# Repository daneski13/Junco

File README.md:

<h1 align="center">Junco</h1>

Named after a small North American bird, Junco is a 60% Raspberry Pi Pico powered split keyboard boasting a 4x6 layout with an aggressive columnar stagger, 2-4 rotary encoders, and per-key RGB lighting.

Want to contribute? Check out [Contributing](./CONTRIBUTING.md).

Junco is inspired by the excellent [crkbd](https://github.com/foostan/crkbd), [Iris](https://keeb.io/collections/iris-split-ergonomic-keyboard/products/iris-keyboard-split-ergonomic-keyboard), [Kimiko](https://github.com/Keycapsss/Kimiko), [Sofle](https://github.com/josefadamcik/SofleKeyboard), and [Ferris](https://github.com/pierrechevalier83/ferris) keyboards. Massive thanks to [@JellyTitan](https://github.com/JellyTitan) for the wiring overhaul.

- [Design Philosophy and Quirks](#design-philosophy-and-quirks)
  - [Philosophy](#philosophy)
  - [Quirks](#quirks)
- [Build Guide / Assembly](#build-guide--assembly)
  - [Parts](#parts)
    - [Required](#required)
    - [Optional - RGB](#optional---rgb)
  - [Soldering](#soldering)
    - [Diodes](#diodes)
    - [RGB (Optional)](#rgb-optional)
    - [Pico](#pico)
    - [Hot-swap Sockets](#hot-swap-sockets)
    - [TRRS jack and Rotary Encoders](#trrs-jack-and-rotary-encoders)
  - [Case](#case)
  - [Flashing the firmware](#flashing-the-firmware)
- [Troubleshooting](#troubleshooting)
  - [No LEDs are working](#no-leds-are-working)
  - [Some LEDs are not working](#some-leds-are-not-working)
  - [An entire row or column of keys is not working](#an-entire-row-or-column-of-keys-is-not-working)
  - [Random key or keys not working](#random-key-or-keys-not-working)

## Design Philosophy and Quirks

### Philosophy

In my search for an ergonomic split keyboard, I came across several great keyboards, but I craved a combination of features and ideas from several with my own flavor. Iris' aesthetics, Kimiko's stagger and layout, elements of Ferris' philosophy.

I also wanted to use Raspberry Pi Picos for the controller as it has many advantages over the ProMicro that is normally used in custom keyboards. At the time, Pico powered keyboards were not yet really a thing and weren't yet supported by the main QMK branch. Thus, I created my own keyboard.

The Junco was designed around a set of goals, similar in vain to the Ferris.

**Goals:**

- Low-Cost
- Raspberry Pi Pico / RP2040
  - Superior flash storage and processing power compared to the common ATMega32 ProMicro
  - Faster than STM32 blackpill with more flash storage at the same cost or less
- Comfort
  - Aggressive Columnar Stagger
- Aesthetics
  - Almost all soldering done on the backside of PCB, optional RGB
- 60% layout
  - Near perfect blend of compactness and easy use without crazy combos or layer gymnastics
- Multiple rotary encoder support
- Hot-swap switches
- Plug and play either side of the split
  - Convenience and traveling
  - Flexible cable management
- Minimal different parts and easy to source
  - No need to buy a different types of LEDs or diodes. No reset switches, capacitors, resistors etc. required.

**Non-goals:**

- Reversible PCB
  - Can make assembly confusing and more error prone
- Multi-switch support
  - MX switches should use MX spacing, Choc switches should use Choc spacing.
- OLED Support
  - OLEDs are an added cost and somewhat comprise the aesthetics in my opinion. Don't find useful for a keyboard, more of a novelty.

### Quirks

Being my first venture into keyboard design... Junco unfortunately suffers from a few "quirks" at the moment that may or may not bother you:

- The case files currently provided in this repo assume PCB mounted switches and uses a 3mm switch plate that is flush with the PCB. This presents some problems that a more proper suspended switch plate would not have:
  - Mounting the Pico on the backside with headers causes a bit of the header to be exposed on the front side of the PCB, so the switch plate provided in this repo will not sit flush with the PCB.
  - The TRRS jack is also soldered on the backside, causing another uneven surface for the switch plate.
  - Thus, material must be removed from the back of the switch plate in the proper places for a flush fit.
    - Heat-gunning the switch plate in the proper area, lining it up with the PCB, and squishing provides a quick and *dirty* solution if done correctly.
  - **PRs are welcome to improve upon the case files or to create new cases as I am a 3D design novice.** A proper fix would be to have the PCB rest on the middle section's lip about 1.5mm below the switch plate. This would also allow plate mounted switches to properly latch onto the switch plate.

## Build Guide / Assembly

### Parts

#### Required

Where "56-58" is the count, 58 is needed with 2 rotary encoders. subtract from 58 every additional encoder (4 encoders 56, with 3 encoders 57).

| Name                                 | Count                   | Remarks                                                                                                                                                                                                                                                                                                                                                                                                                                                     | Potential Storefront                                                                                                                                                                                                                                   |
| ------------------------------------ | ----------------------- | ----------------------------------------------------------------------------------------------------------------------------------------------------------------------------------------------------------------------------------------------------------------------------------------------------------------------------------------------------------------------------------------------------------------------------------------------------------- | ------------------------------------------------------------------------------------------------------------------------------------------------------------------------------------------------------------------------------------------------------ |
| PCB                                  | 2 (1 left and 1 right)  | PCBs can be ordered from manufacturers such as JLCPCB and LCSC                                                                                                                                                                                                                                                                                                                                                                                              |                                                                                                                                                                                                                                                        |
| MX Hot-swap Sockets                  | 56-58                   |                                                                                                                                                                                                                                                                                                                                                                                                                                                             |                                                                                                                                                                                                                                                        |
| Diodes                               | 62                      | Surface mount SOD-123 1N4148, _or_ through-hole 1N4148 diode. These are both common and inexpensive, any one should do. Through hole is usually easier to solder.                                                                                                                                                                                                                                                                                           | SMD: [AliExpress](https://www.aliexpress.us/item/2251832663565152.html) <br>[JLCPCB Part#: C2972760](https://jlcpcb.com/partdetail/3368026-1N4148SOD123/C2972760)<br> Through-hole: [AliExpress](https://www.aliexpress.us/item/2251832473773777.html) |
| Raspberry Pi Picos                   | 2                       | PCB is specifically designed with the official Pico and YD-2040 type clone in mind, however several [other clone types](https://docs.google.com/spreadsheets/d/1LPjy6F5lHfUkmsrM5zlZmc5auYy5YBakW8Awe6hYFWo) should be compatible (Waveshare, WeAct, EstarDyn, Tenstar). Also, the case is currently designed assuming the Pico is soldered with [headers](https://www.sparkfun.com/products/17907), but surface mounting the Pico is supported on the PCB. | [AliExpress, YD-2040](https://www.aliexpress.us/item/3256803909832318.html)                                                                                                                                                                            |
| TRRS Jacks                           | 2                       | PJ-320A                                                                                                                                                                                                                                                                                                                                                                                                                                                     | [AliExpress](https://www.aliexpress.us/item/2255800474897706.html)                                                                                                                                                                                     |
| TRRS Cable (3.5mm "Headphone" Cable) | 1                       | TRRS (4 pole) is currently required, not TRS (3 pole)                                                                                                                                                                                                                                                                                                                                                                                                       |                                                                                                                                                                                                                                                        |
| MX Style Switches                    | 56-58                   |                                                                                                                                                                                                                                                                                                                                                                                                                                                             |                                                                                                                                                                                                                                                        |
| Key Caps                             | 56-58                   |                                                                                                                                                                                                                                                                                                                                                                                                                                                             |                                                                                                                                                                                                                                                        |
| Rotary Encoders and Caps             | 2-4                     | EC-11 Rotary Encoder                                                                                                                                                                                                                                                                                                                                                                                                                                        | [AliExpress](https://www.aliexpress.us/item/2261799870168498.html)                                                                                                                                                                                     |
| M3 6mm or 6mm+ Screws and Nuts       | 8                       |                                                                                                                                                                                                                                                                                                                                                                                                                                                             |                                                                                                                                                                                                                                                        |
| Case                                 | 1 Left Set, 1 Right Set | Case files are located in the [case folder](./Case).                                                                                                                                                                                                                                                                                                                                                                                                        |                                                                                                                                                                                                                                                        |
| Micro USB Cable or USB-C Cable       | 1                       | USB cable for connecting the keyboard to your computer, dependent on what the Pico you chose uses.                                                                                                                                                                                                                                                                                                                                                          |                                                                                                                                                                                                                                                        |

#### Optional - RGB

These parts are necessary for the RGB lighting.

| Name                                          | Count | Remarks                                                                                                                                                                            | Potential Storefront                                                                                                                                                 |
| --------------------------------------------- | ----- | ---------------------------------------------------------------------------------------------------------------------------------------------------------------------------------- | -------------------------------------------------------------------------------------------------------------------------------------------------------------------- |
| 74AHCT1G125 Voltage Level Shifter/ Bus Buffer | 2     | SOT23-5 Footprint <br/> <br/> Required for LEDs to work properly, Pico runs at 3.3V while the LEDs will require 5V                                                                 | [AliExpress](https://www.aliexpress.us/item/3256803831434811.html) <br> [JLCPCB Part# C7484](https://jlcpcb.com/partdetail/TexasInstruments-SN74AHCT1G125DBVR/C7484) |
| RGB SMD LEDs (Prefer SK6803MINI-E)            | 74    | The 3MA SK6803MINI-E is highly recommended over the more traditional 12MA SK6812MINI-E due to its smaller current draw, allowing the LEDs to be very bright at manageable wattage. | [AliExpress](https://www.aliexpress.us/item/3256803450292556.html) <br> [JLCPCB Part# C5184589](https://jlcpcb.com/partdetail/Normand-SK6803MINIE/C5184589)          |

### Soldering

The PCB is not reversible, there is a dedicated right and left half in the KiCad PCB files. Almost all of the soldering will occur on the backside of the PCB. 

#### Diodes

Solder the diodes as you see in the photo.
SMD diodes are soldered on the back of the board. 
Through-hole diodes are inserted on the back of the board, and soldered on the front.

> [!WARNING]
> **Note** that the diodes have polarity, ensure the line on the diode matches the silkscreen.

#### RGB (Optional)

All LEDs must be soldered to the PCB for RGB to work properly, even if you will not be using backlight or will be using an encoder that covers an LED. (They are wired in serial).

First solder the level shifter. It's tiny & squirrley - [drag soldering](https://www.youtube.com/watch?v=wUyetZ5RtPs)" is a good method. See photo:

All LEDs will be soldered facing _down into the board_. The LEDS for per-key RGB will be soldered on the back of the board, while the LED's for the underglow will be soldered on the front of the board.

> [!WARNING]
> **Note** the LED orientation is very important. One of the pads on each LED (the ground pin) will be misshapen relative to the others, this pad should connect to the PCB pad that is marked by the L shape on the silkscreen. For a sanity check, a corner of the LED's front-side will also be "cut", this corner must also line up with the L shape on the silkscreen.

 Blue is LEDs that will be installed on the underside of the board, facing the front-side of the PCB for the per-key lighting. Red will be installed on the front of the board for the underglow:

Per Key leds soldered on the backside, while underglow LEDs ssoldered on the opposite side:

Ground pin orientation:

After you finish the next step of soldering the Pico to the PCB, recommend plugging the keyboard in and flashing QMK to ensure the LEDs are lighting up. If there are any issues, check the troubleshooting section.

#### Pico

If you are soldering the Pico surface mount style, go ahead with soldering it to the backside of the PCB and you can skip to the next section.

If you are soldering the Pico using headers, first solder the Pico to the headers and then the header/Pico to the PCB. 

**Ensure that you are soldering the Pico/Header onto the backside of the PCB.**

The best way to go about this method is to rest the shorter end of the headers in the through-holes of the PCB on a flat surface and place the Pico on top, through the longer end of the header. This will stabilize the headers somewhat and ensure proper spacing. Solder the Pico to the 2 header pins on the both the "top" and "bottom" of the Pico to hold it in place. Proceed to solder the Pico to the rest of the header's pins.

After the Pico is soldered to the header, flip the PCB over and solder the sticking-out header pins to the PCB. Start with the 2 "top" and 2 "bottom" header pins to hold it in place, being sure to minimize the space between the header's plastic and the PCB. Proceed to solder the PCB to the rest of the header's pins.

The end result will look like this:

Backside of PCB:

Front-side of PCB:

#### Hot-swap Sockets

Place hot-swap sockets on the backside of the PCB and solder. See photo:

#### TRRS jack and Rotary Encoders

The process for soldering the TRRS jack and the process for the rotary encoders are very similar.

On the **backside** of the PCB, place the TRRS jack. On the front-side of the PCB, bend the pins of the TRRS jack to "latch" onto the PCB and solder.

Backside PCB:

Front-side PCB:

On the **front-side** of the PCB, place the rotary encoder(s). On the backside of the PCB, bend the pins of the encoder to "latch" onto the PCB and solder.

Front-side PCB:

Backside PCB:

### Case

At the moment, the case files included in the [case directory](./Case) support 3D printing of a case assuming PCB mounted switches (since the 3mm switch plate is resting on the PCB). Since I do not own or have easy access to a 3D printer, the case was designed to be easy to print with 3rd party printing services in-mind such as Treatstock.

Raw files are provided for designing your own case if you see fit. Further work on the case may occur in the future to properly suspend the switch plate. PRs are welcome.

The case is comprised of 4 parts, 8 M3 screws, and 8 M3 nuts.

To have a functional case you need the Bottom Left and Bottom Right along with a Left Switch Plate and a Right Switch Plate. 4 M3 screws and their nuts will hold the switch plate and bottom together for each side of the split. Recommend printing the bottom in white at 40% infill so the underglow LEDs can bleed through.

The naming schemes "- 2 Rotary" and "- 4 Rotary" are products of the raw files used to model the case.

The switch plates named "- 2 Rotary" assume 1 rotary encoder will be used on that side of the split. One by they thumb keys.

The switch plates named "- 4 Rotary" assume 2 rotary encoders will be used on that side of the split. One by the thumb keys and one in the far bottom corner

If you would like to have 3 rotary encoders rather than 2 total or 4 total you would use both variants. The side that will have 2 rotary encoders will use the "- 4 Rotary", while the other side with 1 rotary encoder will use the "- 2 Rotary".

As mentioned in [design quirks](#quirks), there are some problems with making the switch plate flush with the PCB. After you get it flush, you can completely assemble your keyboard! Assembly goes in the reverse of the following:

-- Keycaps --

-- Switches --

-- Case Switch Plate -- (screw + nut connect the plate with the bottom)

-- PCB --

-- Case Bottom --

### Flashing the firmware

Junco is powered by the QMK firmware, see the [build environment setup](https://docs.qmk.fm/#/getting_started_build_tools). Brand new to QMK? Start with the [Complete Newbs Guide](https://docs.qmk.fm/#/newbs).

For users wanting something a little more fun, check out my keymap folder [here](./qmk) and my keymap [here](./qmk/keymaps/deluxe).

Flashing instructions can be found [here](https://github.com/qmk/qmk_firmware/tree/master/keyboards/junco).

Congratulations and enjoy your split keyboard!

## Troubleshooting

### No LEDs are working

Try the following until problem solved:

1. Ensure the level shifter is properly soldered onto the PCB, re-solder as needed.
2. There is a diode without a corresponding switch located to the top right of the Pico on both sides of the split, check and re-solder that diode as needed.
    1. Short the pads on either side of the diode on both halves.
       1. If some the LEDs turn on, re-solder the diodes. Replace it if problem persists.
       2. If no LEDs turn on after shorting the diode's pads, there is likely a problem with the first LED, move to the next section for the first LED in the electrical order. If that still doesn't work, the level shifter is likely damaged and needs to be replaced.

### Some LEDs are not working

Go through the LED electrical order (pictured below) until you reach the problem LED. That LED **or** the one previous to it has a problem.

LED Electrical Order (1-8 are underglow):

Right side is identical but mirrored.

Try the following until problem solved:

1. Check that the pads of LED not turning on and its previous are soldered correctly, re-solder for a better connection as needed.
2. Double check that the LED not turning on is in the correct orientation.
3. If the soldering looks good and the orientation is correct, try re-soldering all the pads any way for good measure.
4. If re-soldering didn't work than the LED is likely dead or damaged in which case replace it.

### An entire row or column of keys is not working

In this case, there is most likely a problem with the PCB's connection to the Pico. Note that the bottom row of keys is staggered by 2, so the the corresponding matrix column is shifted.

Rows:

Cols:

The right side is identical but mirrored.

Try the following until problem solved:

1. Double check that you have soldered the Pico into the correct holes.
2. Ensure the soldering connections of the Pico to the PCB is good (if you used a header to solder the Pico onto the PCB one of the connections to the through-hole is likely bad). Re-solder as needed.
3. If none of the connections are obviously bad, use the image above to see what row/column corresponds to what connection (GP numbering on back of PCB). Re-solder that specific connection for good measure and test.
4. If re-soldering the connection didn't work, your Pico or PCB is likely damaged. Rule out the Pico by directly shorting the that row or column's corresponding pad on the Pico with another column/row pad (connecting one row and one column). If a key press is registered, there is a problem with your PCB, see the bottom of the next section about potentially fixing paths on the PCB. If no keypress is registered, the Pico is damaged and have fun de-soldering your Pico (hot-air station or careful work with a heat gun is the best way).

### Random key or keys not working

Note that the bottom row of keys is staggered by 2, so the the corresponding matrix column is shifted. See the photo in the above section.

If it's not a row or column of keys, than there is a bad connection between your switch and PCB.

Try the following until problem solved:

1. Re-seat the switch in the hot-swap socket.
2. Try a different switch.
3. Check the soldering of the hot-swap socket to the PCB, re-solder as needed
4. Short the PCB pads on either side of the hot-swap socket, if that registers a keypress, the hot-swap socket is bad and needs to replaced.
5. Check the diode.
   1. Check the soldering of the diode to the PCB and re-solder as needed.
   2. Double check that the diode is oriented correctly.
   3. Make sure diode actually works and has a good connection.
      1. Read the diode with a multimeter, typically reads a little more than 0.6. Higher numbers usually means the solder connection is bad, de-solder and re-solder the diode. If not reading, diode is bad and needs to be replaced.
      2. No multimeter? Short either side of the diode and press the key. If that works either the diode's connection is bad and re-solder, or the diode is dead and needs to be replaced.
6. If none of the above worked, the problem is most likely with the paths inside the PCB.
   1. You can try the following: (credit to [crkbd](https://github.com/foostan/crkbd) guide)
      1. "Visually inspect the PCB. If it looks scratched or damaged anywhere along the path from ProMicro to diode to keyswitch, the path might be interrupted. If you find a spot that looks damaged, you can use some wire to bypass the section that is damaged (e.g. connecting the ProMicro directly to the first pad of the diode). If this fixes the key, then you can either opt to keep the wire permanently, or you can try to repair the path. The path can be repaired by carefully scraping off the paint from a section of the path that is okay on either side of the damaged part (use a small flat head screwdriver intended for electronics). Then clean carefully with alcohol and solder a new connection. Youtube might have some guides on how to do this."

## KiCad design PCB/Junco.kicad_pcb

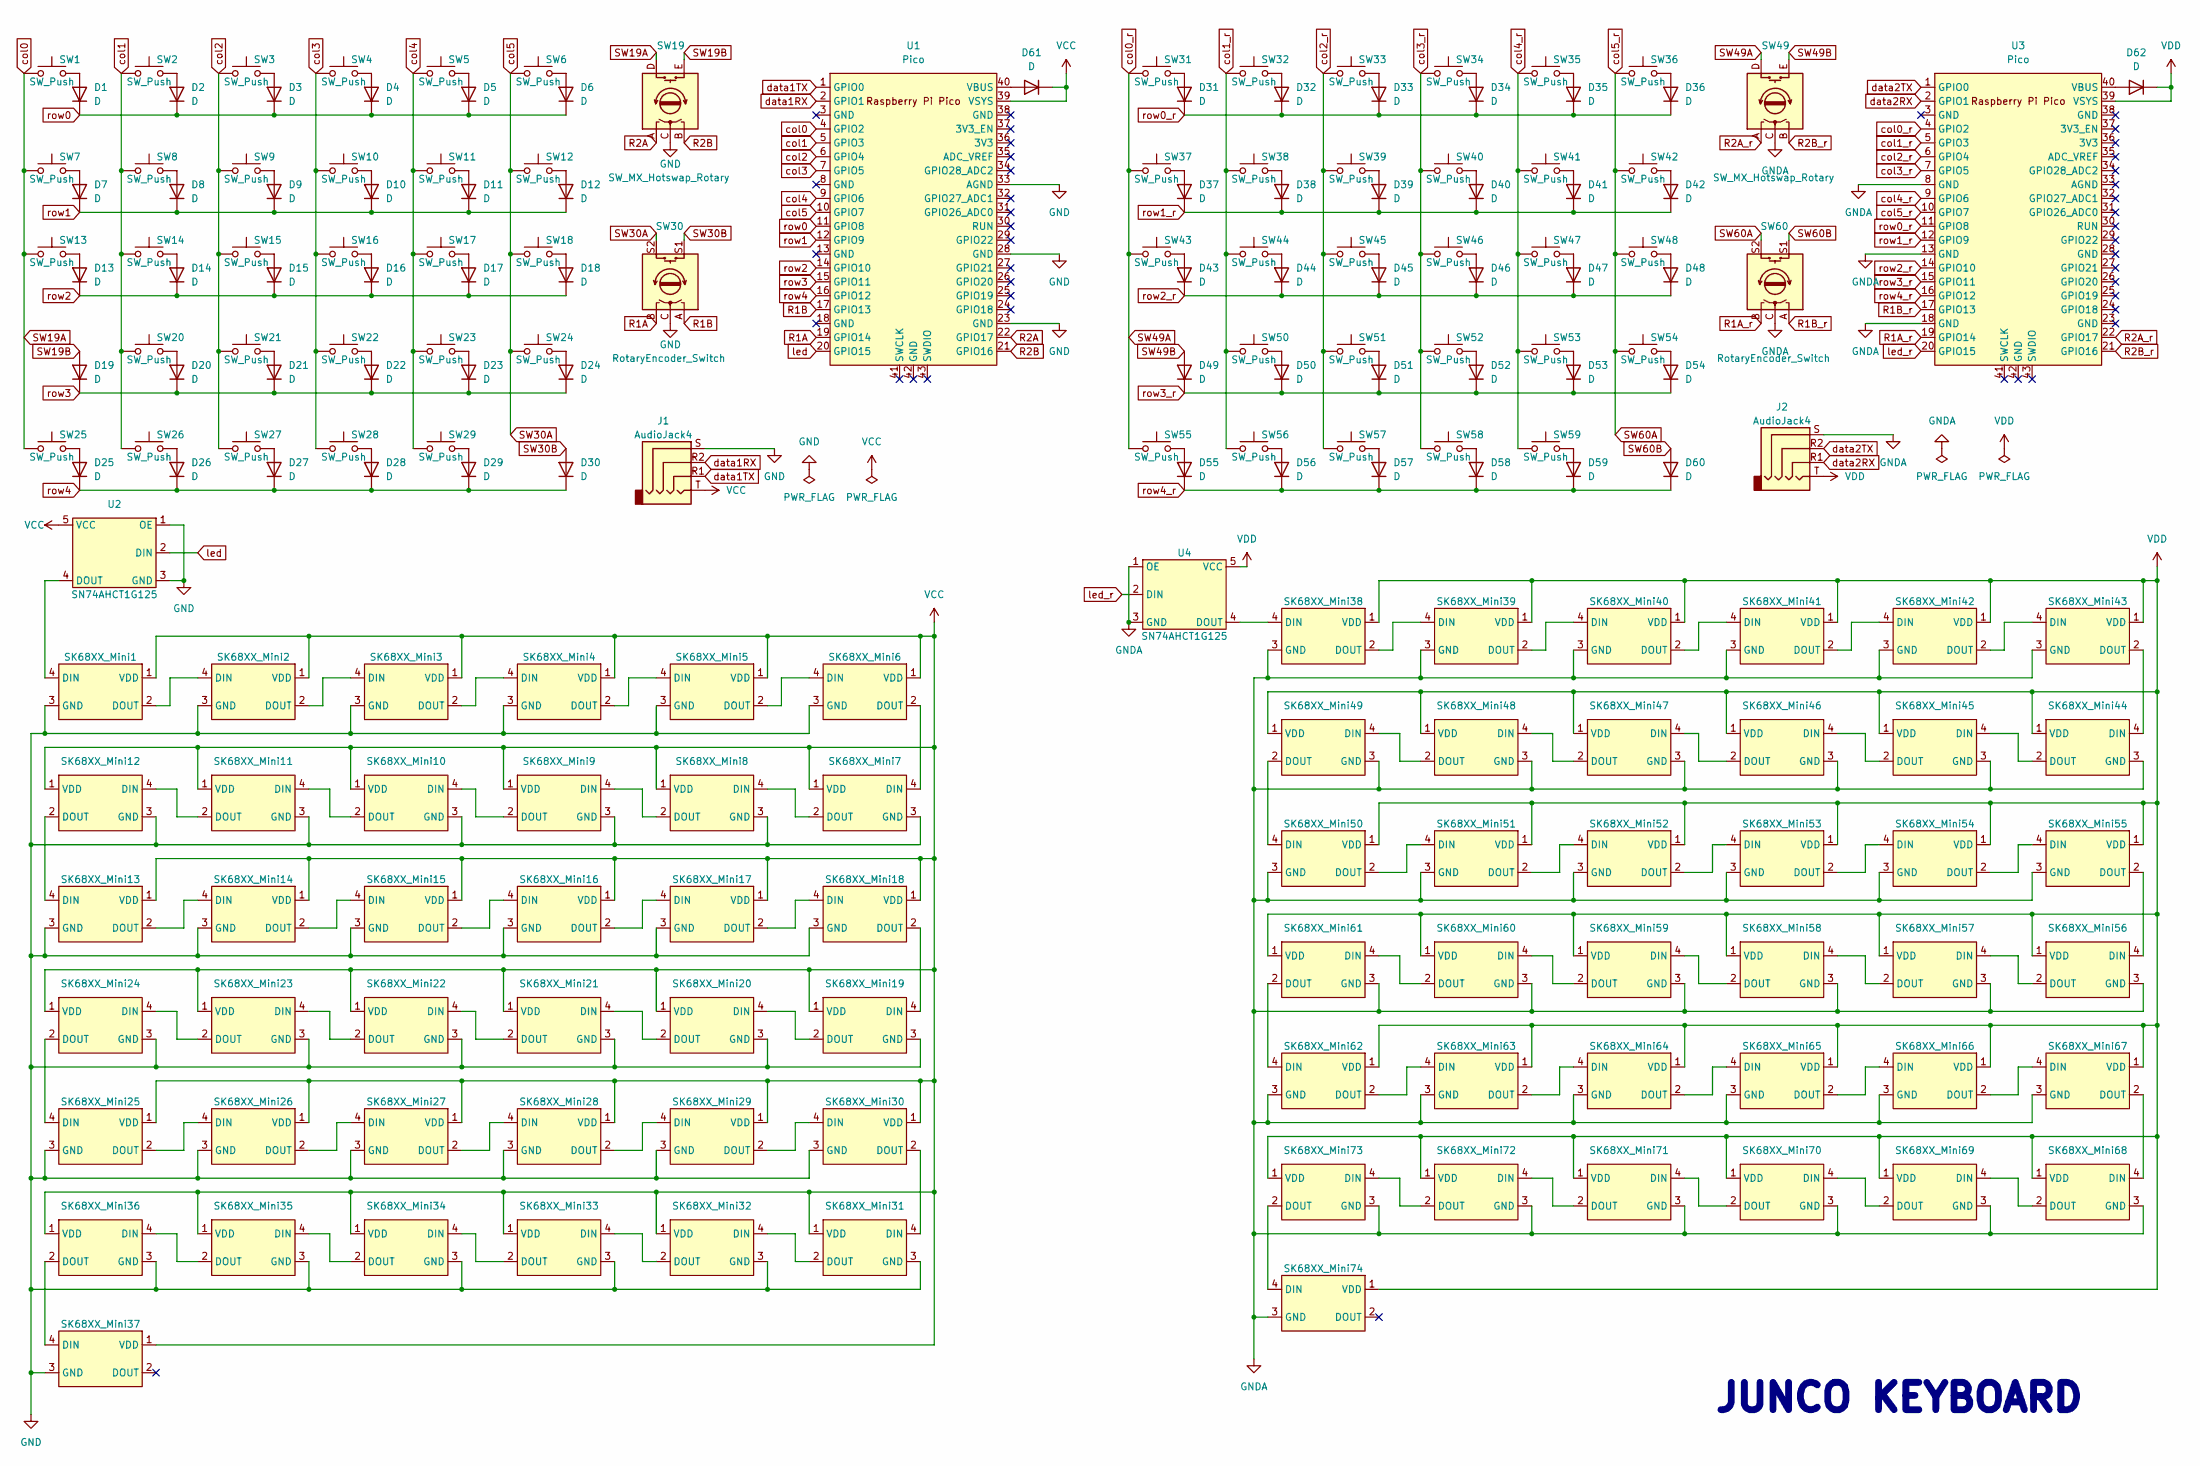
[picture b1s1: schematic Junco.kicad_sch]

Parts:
D1, D2, D3, D4, D5, D6, D7, D8, D9, D10, D11, D12, D13, D14, D15, D16, D17, D18, D19, D20, D21, D22, D23, D24, D25, D26, D27, D28, D29, D30, D31, D32, D33, D34, D35, D36, D37, D38, D39, D40, D41, D42, D43, D44, D45, D46, D47, D48, D49, D50, D51, D52, D53, D54, D55, D56, D57, D58, D59, D60, D61, D62: D; D_SOD-123
J1, J2: AudioJack4; TRRS_PJ320A
SK68XX_Mini1, SK68XX_Mini2, SK68XX_Mini3, SK68XX_Mini4, SK68XX_Mini5, SK68XX_Mini6, SK68XX_Mini7, SK68XX_Mini8, SK68XX_Mini38, SK68XX_Mini39, SK68XX_Mini40, SK68XX_Mini41, SK68XX_Mini42, SK68XX_Mini43, SK68XX_Mini44, SK68XX_Mini45: SK68XXMini
SK68XX_Mini9, SK68XX_Mini10, SK68XX_Mini11, SK68XX_Mini12, SK68XX_Mini13, SK68XX_Mini14, SK68XX_Mini21, SK68XX_Mini22, SK68XX_Mini23, SK68XX_Mini24, SK68XX_Mini25, SK68XX_Mini26, SK68XX_Mini35, SK68XX_Mini36, SK68XX_Mini37, SK68XX_Mini52, SK68XX_Mini53, SK68XX_Mini54, SK68XX_Mini55, SK68XX_Mini56, SK68XX_Mini57, SK68XX_Mini64, SK68XX_Mini65, SK68XX_Mini66, SK68XX_Mini67, SK68XX_Mini68, SK68XX_Mini69, SK68XX_Mini70, SK68XX_Mini71: SK68XXMini; SK68XXMini_Offset_Flipped
SK68XX_Mini15, SK68XX_Mini16, SK68XX_Mini17, SK68XX_Mini18, SK68XX_Mini19, SK68XX_Mini20, SK68XX_Mini27, SK68XX_Mini28, SK68XX_Mini29, SK68XX_Mini30, SK68XX_Mini31, SK68XX_Mini32, SK68XX_Mini33, SK68XX_Mini34, SK68XX_Mini46, SK68XX_Mini47, SK68XX_Mini48, SK68XX_Mini49, SK68XX_Mini50, SK68XX_Mini51, SK68XX_Mini58, SK68XX_Mini59, SK68XX_Mini60, SK68XX_Mini61, SK68XX_Mini62, SK68XX_Mini63, SK68XX_Mini72, SK68XX_Mini73, SK68XX_Mini74: SK68XXMini; SK68XXMini_Offset
SW1, SW2, SW3, SW4, SW5, SW6, SW7, SW8, SW9, SW10, SW11, SW12, SW13, SW14, SW15, SW16, SW17, SW18, SW20, SW21, SW22, SW23, SW24, SW25, SW26, SW27, SW31, SW32, SW33, SW34, SW35, SW36, SW37, SW38, SW39, SW40, SW41, SW42, SW43, SW44, SW45, SW46, SW47, SW48, SW50, SW51, SW52, SW53, SW54, SW55, SW56, SW57: SW_Push; SW_MX_HS_1u
SW19, SW49: SW_MX_Hotswap_Rotary
SW28, SW29, SW58, SW59: SW_Push; SW_MX_HS_1.5u
SW30, SW60: RotaryEncoder_Switch; EC11_Rotary_Encoder
U1, U3: Pico; RPi_Pico_SMD_TH
U2, U4: SN74AHCT1G125

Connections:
GND: J1.S, SK68XX_Mini1.3 (GND), SK68XX_Mini2.3 (GND), SK68XX_Mini3.3 (GND), SK68XX_Mini4.3 (GND), SK68XX_Mini5.3 (GND), SK68XX_Mini6.3 (GND), SK68XX_Mini7.3 (GND), SK68XX_Mini8.3 (GND), SK68XX_Mini9.3 (GND), SK68XX_Mini10.3 (GND), SK68XX_Mini11.3 (GND), SK68XX_Mini12.3 (GND), SK68XX_Mini13.3 (GND), SK68XX_Mini14.3 (GND), SK68XX_Mini15.3 (GND), SK68XX_Mini16.3 (GND), SK68XX_Mini17.3 (GND), SK68XX_Mini18.3 (GND), SK68XX_Mini19.3 (GND), SK68XX_Mini20.3 (GND), SK68XX_Mini21.3 (GND), SK68XX_Mini22.3 (GND), SK68XX_Mini23.3 (GND), SK68XX_Mini24.3 (GND), SK68XX_Mini25.3 (GND), SK68XX_Mini26.3 (GND), SK68XX_Mini27.3 (GND), SK68XX_Mini28.3 (GND), SK68XX_Mini29.3 (GND), SK68XX_Mini30.3 (GND), SK68XX_Mini31.3 (GND), SK68XX_Mini32.3 (GND), SK68XX_Mini33.3 (GND), SK68XX_Mini34.3 (GND), SK68XX_Mini35.3 (GND), SK68XX_Mini36.3 (GND), SK68XX_Mini37.3 (GND), SW19.C, SW30.C, U1.23 (GND), U1.28 (GND), U1.33 (AGND), U2.1 (OE), U2.3 (GND)
GNDA: J2.S, SK68XX_Mini38.3 (GND), SK68XX_Mini39.3 (GND), SK68XX_Mini40.3 (GND), SK68XX_Mini41.3 (GND), SK68XX_Mini42.3 (GND), SK68XX_Mini43.3 (GND), SK68XX_Mini44.3 (GND), SK68XX_Mini45.3 (GND), SK68XX_Mini46.3 (GND), SK68XX_Mini47.3 (GND), SK68XX_Mini48.3 (GND), SK68XX_Mini49.3 (GND), SK68XX_Mini50.3 (GND), SK68XX_Mini51.3 (GND), SK68XX_Mini52.3 (GND), SK68XX_Mini53.3 (GND), SK68XX_Mini54.3 (GND), SK68XX_Mini55.3 (GND), SK68XX_Mini56.3 (GND), SK68XX_Mini57.3 (GND), SK68XX_Mini58.3 (GND), SK68XX_Mini59.3 (GND), SK68XX_Mini60.3 (GND), SK68XX_Mini61.3 (GND), SK68XX_Mini62.3 (GND), SK68XX_Mini63.3 (GND), SK68XX_Mini64.3 (GND), SK68XX_Mini65.3 (GND), SK68XX_Mini66.3 (GND), SK68XX_Mini67.3 (GND), SK68XX_Mini68.3 (GND), SK68XX_Mini69.3 (GND), SK68XX_Mini70.3 (GND), SK68XX_Mini71.3 (GND), SK68XX_Mini72.3 (GND), SK68XX_Mini73.3 (GND), SK68XX_Mini74.3 (GND), SW49.C, SW60.C, U3.8 (GND), U3.13 (GND), U3.18 (GND), U4.1 (OE), U4.3 (GND)
unnamed: D1.2 (A), SW1.2
unnamed: D2.2 (A), SW2.2
unnamed: D3.2 (A), SW3.2
unnamed: D4.2 (A), SW4.2
unnamed: D5.2 (A), SW5.2
unnamed: D6.2 (A), SW6.2
unnamed: D7.2 (A), SW7.2
unnamed: D8.2 (A), SW8.2
unnamed: D9.2 (A), SW9.2
unnamed: D10.2 (A), SW10.2
unnamed: D11.2 (A), SW11.2
unnamed: D12.2 (A), SW12.2
unnamed: D13.2 (A), SW13.2
unnamed: D14.2 (A), SW14.2
unnamed: D15.2 (A), SW15.2
unnamed: D16.2 (A), SW16.2
unnamed: D17.2 (A), SW17.2
unnamed: D18.2 (A), SW18.2
unnamed: D20.2 (A), SW20.2
unnamed: D21.2 (A), SW21.2
unnamed: D22.2 (A), SW22.2
unnamed: D23.2 (A), SW23.2
unnamed: D24.2 (A), SW24.2
unnamed: D25.2 (A), SW25.2
unnamed: D26.2 (A), SW26.2
unnamed: D27.2 (A), SW27.2
unnamed: D28.2 (A), SW28.2
unnamed: D29.2 (A), SW29.2
unnamed: D31.2 (A), SW31.2
unnamed: D32.2 (A), SW32.2
unnamed: D33.2 (A), SW33.2
unnamed: D34.2 (A), SW34.2
unnamed: D35.2 (A), SW35.2
unnamed: D36.2 (A), SW36.2
unnamed: D37.2 (A), SW37.2
unnamed: D38.2 (A), SW38.2
unnamed: D39.2 (A), SW39.2
unnamed: D40.2 (A), SW40.2
unnamed: D41.2 (A), SW41.2
unnamed: D42.2 (A), SW42.2
unnamed: D43.2 (A), SW43.2
unnamed: D44.2 (A), SW44.2
unnamed: D45.2 (A), SW45.2
unnamed: D46.2 (A), SW46.2
unnamed: D47.2 (A), SW47.2
unnamed: D48.2 (A), SW48.2
unnamed: D50.2 (A), SW50.2
unnamed: D51.2 (A), SW51.2
unnamed: D52.2 (A), SW52.2
unnamed: D53.2 (A), SW53.2
unnamed: D54.2 (A), SW54.2
unnamed: D55.2 (A), SW55.2
unnamed: D56.2 (A), SW56.2
unnamed: D57.2 (A), SW57.2
unnamed: D58.2 (A), SW58.2
unnamed: D59.2 (A), SW59.2
unnamed: D61.2 (A), U1.40 (VBUS)
unnamed: D62.2 (A), U3.40 (VBUS)
unnamed: SK68XX_Mini1.2 (DOUT), SK68XX_Mini2.4 (DIN)
unnamed: SK68XX_Mini1.4 (DIN), U2.4 (DOUT)
unnamed: SK68XX_Mini2.2 (DOUT), SK68XX_Mini3.4 (DIN)
unnamed: SK68XX_Mini3.2 (DOUT), SK68XX_Mini4.4 (DIN)
unnamed: SK68XX_Mini4.2 (DOUT), SK68XX_Mini5.4 (DIN)
unnamed: SK68XX_Mini5.2 (DOUT), SK68XX_Mini6.4 (DIN)
unnamed: SK68XX_Mini6.2 (DOUT), SK68XX_Mini7.4 (DIN)
unnamed: SK68XX_Mini7.2 (DOUT), SK68XX_Mini8.4 (DIN)
unnamed: SK68XX_Mini8.2 (DOUT), SK68XX_Mini9.4 (DIN)
unnamed: SK68XX_Mini10.2 (DOUT), SK68XX_Mini11.4 (DIN)
unnamed: SK68XX_Mini9.2 (DOUT), SK68XX_Mini10.4 (DIN)
unnamed: SK68XX_Mini11.2 (DOUT), SK68XX_Mini12.4 (DIN)
unnamed: SK68XX_Mini12.2 (DOUT), SK68XX_Mini13.4 (DIN)
unnamed: SK68XX_Mini13.2 (DOUT), SK68XX_Mini14.4 (DIN)
unnamed: SK68XX_Mini14.2 (DOUT), SK68XX_Mini15.4 (DIN)
unnamed: SK68XX_Mini15.2 (DOUT), SK68XX_Mini16.4 (DIN)
unnamed: SK68XX_Mini16.2 (DOUT), SK68XX_Mini17.4 (DIN)
unnamed: SK68XX_Mini17.2 (DOUT), SK68XX_Mini18.4 (DIN)
unnamed: SK68XX_Mini18.2 (DOUT), SK68XX_Mini19.4 (DIN)
unnamed: SK68XX_Mini19.2 (DOUT), SK68XX_Mini20.4 (DIN)
unnamed: SK68XX_Mini20.2 (DOUT), SK68XX_Mini21.4 (DIN)
unnamed: SK68XX_Mini21.2 (DOUT), SK68XX_Mini22.4 (DIN)
unnamed: SK68XX_Mini22.2 (DOUT), SK68XX_Mini23.4 (DIN)
unnamed: SK68XX_Mini23.2 (DOUT), SK68XX_Mini24.4 (DIN)
unnamed: SK68XX_Mini24.2 (DOUT), SK68XX_Mini25.4 (DIN)
unnamed: SK68XX_Mini25.2 (DOUT), SK68XX_Mini26.4 (DIN)
unnamed: SK68XX_Mini26.2 (DOUT), SK68XX_Mini27.4 (DIN)
unnamed: SK68XX_Mini27.2 (DOUT), SK68XX_Mini28.4 (DIN)
unnamed: SK68XX_Mini28.2 (DOUT), SK68XX_Mini29.4 (DIN)
unnamed: SK68XX_Mini29.2 (DOUT), SK68XX_Mini30.4 (DIN)
unnamed: SK68XX_Mini30.2 (DOUT), SK68XX_Mini31.4 (DIN)
unnamed: SK68XX_Mini31.2 (DOUT), SK68XX_Mini32.4 (DIN)
unnamed: SK68XX_Mini32.2 (DOUT), SK68XX_Mini33.4 (DIN)
unnamed: SK68XX_Mini33.2 (DOUT), SK68XX_Mini34.4 (DIN)
unnamed: SK68XX_Mini34.2 (DOUT), SK68XX_Mini35.4 (DIN)
unnamed: SK68XX_Mini35.2 (DOUT), SK68XX_Mini36.4 (DIN)
unnamed: SK68XX_Mini36.2 (DOUT), SK68XX_Mini37.4 (DIN)
unnamed: SK68XX_Mini38.2 (DOUT), SK68XX_Mini39.4 (DIN)
unnamed: SK68XX_Mini38.4 (DIN), U4.4 (DOUT)
unnamed: SK68XX_Mini39.2 (DOUT), SK68XX_Mini40.4 (DIN)
unnamed: SK68XX_Mini40.2 (DOUT), SK68XX_Mini41.4 (DIN)
unnamed: SK68XX_Mini41.2 (DOUT), SK68XX_Mini42.4 (DIN)
unnamed: SK68XX_Mini42.2 (DOUT), SK68XX_Mini43.4 (DIN)
unnamed: SK68XX_Mini43.2 (DOUT), SK68XX_Mini44.4 (DIN)
unnamed: SK68XX_Mini44.2 (DOUT), SK68XX_Mini45.4 (DIN)
unnamed: SK68XX_Mini45.2 (DOUT), SK68XX_Mini46.4 (DIN)
unnamed: SK68XX_Mini46.2 (DOUT), SK68XX_Mini47.4 (DIN)
unnamed: SK68XX_Mini47.2 (DOUT), SK68XX_Mini48.4 (DIN)
unnamed: SK68XX_Mini48.2 (DOUT), SK68XX_Mini49.4 (DIN)
unnamed: SK68XX_Mini49.2 (DOUT), SK68XX_Mini50.4 (DIN)
unnamed: SK68XX_Mini50.2 (DOUT), SK68XX_Mini51.4 (DIN)
unnamed: SK68XX_Mini51.2 (DOUT), SK68XX_Mini52.4 (DIN)
unnamed: SK68XX_Mini52.2 (DOUT), SK68XX_Mini53.4 (DIN)
unnamed: SK68XX_Mini53.2 (DOUT), SK68XX_Mini54.4 (DIN)
unnamed: SK68XX_Mini54.2 (DOUT), SK68XX_Mini55.4 (DIN)
unnamed: SK68XX_Mini55.2 (DOUT), SK68XX_Mini56.4 (DIN)
unnamed: SK68XX_Mini56.2 (DOUT), SK68XX_Mini57.4 (DIN)
unnamed: SK68XX_Mini57.2 (DOUT), SK68XX_Mini58.4 (DIN)
unnamed: SK68XX_Mini58.2 (DOUT), SK68XX_Mini59.4 (DIN)
unnamed: SK68XX_Mini59.2 (DOUT), SK68XX_Mini60.4 (DIN)
unnamed: SK68XX_Mini60.2 (DOUT), SK68XX_Mini61.4 (DIN)
unnamed: SK68XX_Mini61.2 (DOUT), SK68XX_Mini62.4 (DIN)
unnamed: SK68XX_Mini62.2 (DOUT), SK68XX_Mini63.4 (DIN)
unnamed: SK68XX_Mini63.2 (DOUT), SK68XX_Mini64.4 (DIN)
unnamed: SK68XX_Mini64.2 (DOUT), SK68XX_Mini65.4 (DIN)
unnamed: SK68XX_Mini65.2 (DOUT), SK68XX_Mini66.4 (DIN)
unnamed: SK68XX_Mini66.2 (DOUT), SK68XX_Mini67.4 (DIN)
unnamed: SK68XX_Mini67.2 (DOUT), SK68XX_Mini68.4 (DIN)
unnamed: SK68XX_Mini68.2 (DOUT), SK68XX_Mini69.4 (DIN)
unnamed: SK68XX_Mini69.2 (DOUT), SK68XX_Mini70.4 (DIN)
unnamed: SK68XX_Mini70.2 (DOUT), SK68XX_Mini71.4 (DIN)
unnamed: SK68XX_Mini71.2 (DOUT), SK68XX_Mini72.4 (DIN)
unnamed: SK68XX_Mini72.2 (DOUT), SK68XX_Mini73.4 (DIN)
unnamed: SK68XX_Mini73.2 (DOUT), SK68XX_Mini74.4 (DIN)
R1A: SW30.B, U1.19 (GPIO14)
R1A_r: SW60.B, U3.19 (GPIO14)
R1B: SW30.A, U1.17 (GPIO13)
R1B_r: SW60.A, U3.17 (GPIO13)
R2A: SW19.A, U1.22 (GPIO17)
R2A_r: SW49.A, U3.22 (GPIO17)
R2B: SW19.B, U1.21 (GPIO16)
R2B_r: SW49.B, U3.21 (GPIO16)
SW19A: SW1.1, SW7.1, SW13.1, SW19.1 (SW), SW19.D (S1), SW25.1, U1.4 (GPIO2)
SW19B: D19.2 (A), SW19.2 (SW), SW19.E (S2)
SW30A: SW6.1, SW12.1, SW18.1, SW24.1, SW30.S2, U1.10 (GPIO7)
SW30B: D30.2 (A), SW30.S1
SW49A: SW31.1, SW37.1, SW43.1, SW49.1 (SW), SW49.D (S1), SW55.1, U3.4 (GPIO2)
SW49B: D49.2 (A), SW49.2 (SW), SW49.E (S2)
SW60A: SW36.1, SW42.1, SW48.1, SW54.1, SW60.S2, U3.10 (GPIO7)
SW60B: D60.2 (A), SW60.S1
VCC: D61.1 (K), J1.T, SK68XX_Mini1.1 (VDD), SK68XX_Mini2.1 (VDD), SK68XX_Mini3.1 (VDD), SK68XX_Mini4.1 (VDD), SK68XX_Mini5.1 (VDD), SK68XX_Mini6.1 (VDD), SK68XX_Mini7.1 (VDD), SK68XX_Mini8.1 (VDD), SK68XX_Mini9.1 (VDD), SK68XX_Mini10.1 (VDD), SK68XX_Mini11.1 (VDD), SK68XX_Mini12.1 (VDD), SK68XX_Mini13.1 (VDD), SK68XX_Mini14.1 (VDD), SK68XX_Mini15.1 (VDD), SK68XX_Mini16.1 (VDD), SK68XX_Mini17.1 (VDD), SK68XX_Mini18.1 (VDD), SK68XX_Mini19.1 (VDD), SK68XX_Mini20.1 (VDD), SK68XX_Mini21.1 (VDD), SK68XX_Mini22.1 (VDD), SK68XX_Mini23.1 (VDD), SK68XX_Mini24.1 (VDD), SK68XX_Mini25.1 (VDD), SK68XX_Mini26.1 (VDD), SK68XX_Mini27.1 (VDD), SK68XX_Mini28.1 (VDD), SK68XX_Mini29.1 (VDD), SK68XX_Mini30.1 (VDD), SK68XX_Mini31.1 (VDD), SK68XX_Mini32.1 (VDD), SK68XX_Mini33.1 (VDD), SK68XX_Mini34.1 (VDD), SK68XX_Mini35.1 (VDD), SK68XX_Mini36.1 (VDD), SK68XX_Mini37.1 (VDD), U1.39 (VSYS), U2.5 (VCC)
VDD: D62.1 (K), J2.T, SK68XX_Mini38.1 (VDD), SK68XX_Mini39.1 (VDD), SK68XX_Mini40.1 (VDD), SK68XX_Mini41.1 (VDD), SK68XX_Mini42.1 (VDD), SK68XX_Mini43.1 (VDD), SK68XX_Mini44.1 (VDD), SK68XX_Mini45.1 (VDD), SK68XX_Mini46.1 (VDD), SK68XX_Mini47.1 (VDD), SK68XX_Mini48.1 (VDD), SK68XX_Mini49.1 (VDD), SK68XX_Mini50.1 (VDD), SK68XX_Mini51.1 (VDD), SK68XX_Mini52.1 (VDD), SK68XX_Mini53.1 (VDD), SK68XX_Mini54.1 (VDD), SK68XX_Mini55.1 (VDD), SK68XX_Mini56.1 (VDD), SK68XX_Mini57.1 (VDD), SK68XX_Mini58.1 (VDD), SK68XX_Mini59.1 (VDD), SK68XX_Mini60.1 (VDD), SK68XX_Mini61.1 (VDD), SK68XX_Mini62.1 (VDD), SK68XX_Mini63.1 (VDD), SK68XX_Mini64.1 (VDD), SK68XX_Mini65.1 (VDD), SK68XX_Mini66.1 (VDD), SK68XX_Mini67.1 (VDD), SK68XX_Mini68.1 (VDD), SK68XX_Mini69.1 (VDD), SK68XX_Mini70.1 (VDD), SK68XX_Mini71.1 (VDD), SK68XX_Mini72.1 (VDD), SK68XX_Mini73.1 (VDD), SK68XX_Mini74.1 (VDD), U3.39 (VSYS), U4.5 (VCC)
col1: SW2.1, SW8.1, SW14.1, SW20.1, SW26.1, U1.5 (GPIO3)
col1_r: SW32.1, SW38.1, SW44.1, SW50.1, SW56.1, U3.5 (GPIO3)
col2: SW3.1, SW9.1, SW15.1, SW21.1, SW27.1, U1.6 (GPIO4)
col2_r: SW33.1, SW39.1, SW45.1, SW51.1, SW57.1, U3.6 (GPIO4)
col3: SW4.1, SW10.1, SW16.1, SW22.1, SW28.1, U1.7 (GPIO5)
col3_r: SW34.1, SW40.1, SW46.1, SW52.1, SW58.1, U3.7 (GPIO5)
col4: SW5.1, SW11.1, SW17.1, SW23.1, SW29.1, U1.9 (GPIO6)
col4_r: SW35.1, SW41.1, SW47.1, SW53.1, SW59.1, U3.9 (GPIO6)
data1RX: J1.R2, U1.2 (GPIO1)
data1TX: J1.R1, U1.1 (GPIO0)
data2RX: J2.R1, U3.2 (GPIO1)
data2TX: J2.R2, U3.1 (GPIO0)
led: U1.20 (GPIO15), U2.2 (DIN)
led_r: U3.20 (GPIO15), U4.2 (DIN)
row0: D1.1 (K), D2.1 (K), D3.1 (K), D4.1 (K), D5.1 (K), D6.1 (K), U1.11 (GPIO8)
row0_r: D31.1 (K), D32.1 (K), D33.1 (K), D34.1 (K), D35.1 (K), D36.1 (K), U3.11 (GPIO8)
row1: D7.1 (K), D8.1 (K), D9.1 (K), D10.1 (K), D11.1 (K), D12.1 (K), U1.12 (GPIO9)
row1_r: D37.1 (K), D38.1 (K), D39.1 (K), D40.1 (K), D41.1 (K), D42.1 (K), U3.12 (GPIO9)
row2: D13.1 (K), D14.1 (K), D15.1 (K), D16.1 (K), D17.1 (K), D18.1 (K), U1.14 (GPIO10)
row2_r: D43.1 (K), D44.1 (K), D45.1 (K), D46.1 (K), D47.1 (K), D48.1 (K), U3.14 (GPIO10)
row3: D19.1 (K), D20.1 (K), D21.1 (K), D22.1 (K), D23.1 (K), D24.1 (K), U1.15 (GPIO11)
row3_r: D49.1 (K), D50.1 (K), D51.1 (K), D52.1 (K), D53.1 (K), D54.1 (K), U3.15 (GPIO11)
row4: D25.1 (K), D26.1 (K), D27.1 (K), D28.1 (K), D29.1 (K), D30.1 (K), U1.16 (GPIO12)
row4_r: D55.1 (K), D56.1 (K), D57.1 (K), D58.1 (K), D59.1 (K), D60.1 (K), U3.16 (GPIO12)

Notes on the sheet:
JUNCO KEYBOARD

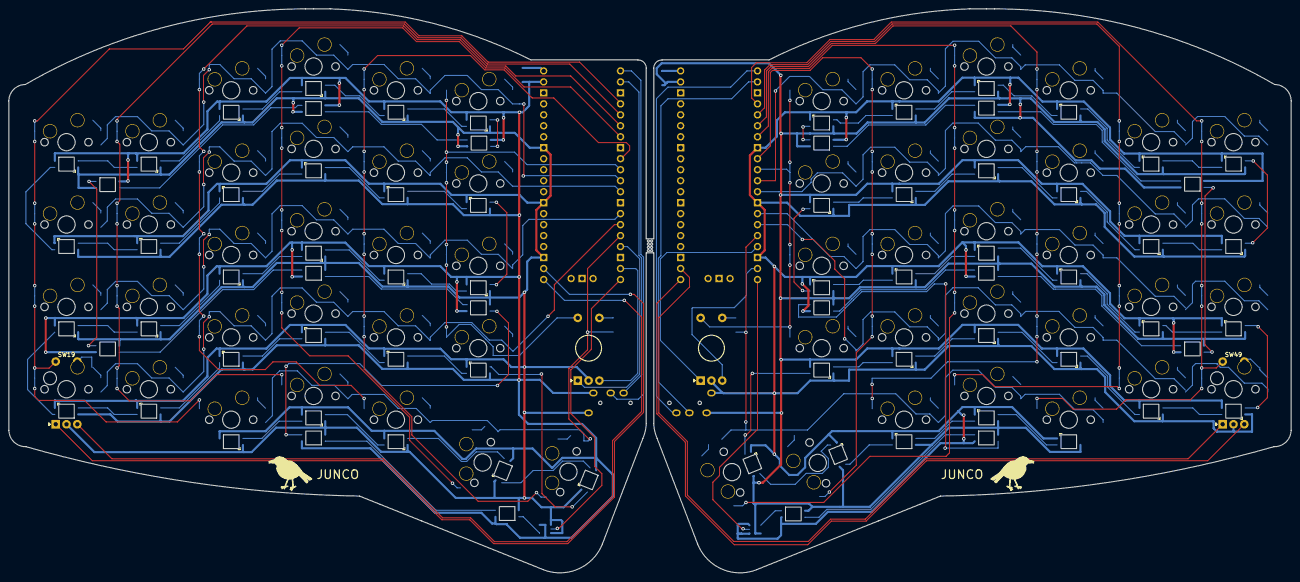
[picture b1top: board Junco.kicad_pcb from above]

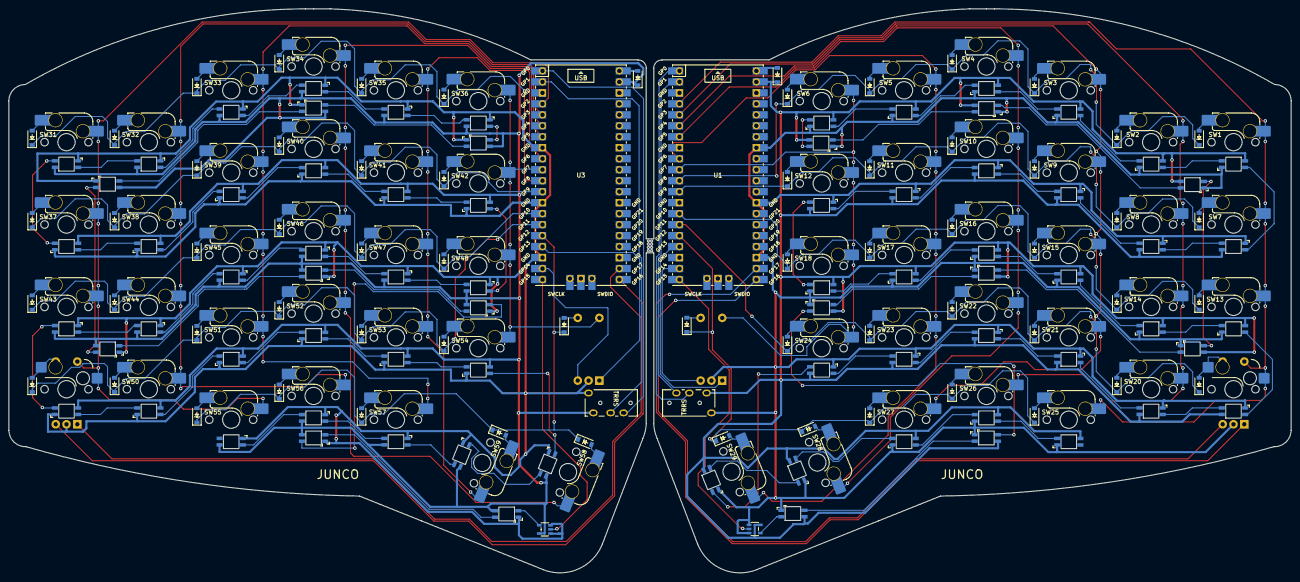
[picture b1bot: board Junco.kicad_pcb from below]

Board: 2 copper layers, 296.6 x 130.5 mm, 203 parts (62 on the bottom side), 176 nets.

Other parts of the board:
Ref**: Val**; Junco

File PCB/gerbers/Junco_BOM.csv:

"Id";"Designator";"Footprint";"Quantity";"Designation";"Supplier and ref";
1;"D40,D6,D28,D58,D26,D51,D52,D8,D12,D42,D30,D29,D43,D21,D53,D31,D11,D47,D41,D45,D39,D35,D24,D44,D9,D5,D36,D61,D20,D3,D50,D38,D62,D27,D16,D18,D22,D54,D2,D46,D48,D57,D17,D37,D60,D59,D7,D23,D19,D55,D15,D32,D14,D25,D49,D33,D34,D1,D4,D10,D13,D56";"D_SOD-123_DO-35_Hybrid_DoubleSided_V2";62;"D";;;
2;"SK68XX_Mini14,SK68XX_Mini17,SK68XX_Mini50,SK68XX_Mini12,SK68XX_Mini32,SK68XX_Mini67,SK68XX_Mini10,SK68XX_Mini47,SK68XX_Mini74,SK68XX_Mini16,SK68XX_Mini46,SK68XX_Mini26,SK68XX_Mini22,SK68XX_Mini56,SK68XX_Mini23,SK68XX_Mini37,SK68XX_Mini53,SK68XX_Mini24,SK68XX_Mini19,SK68XX_Mini57,SK68XX_Mini59,SK68XX_Mini48,SK68XX_Mini70,SK68XX_Mini21,SK68XX_Mini65,SK68XX_Mini20,SK68XX_Mini36,SK68XX_Mini58,SK68XX_Mini63,SK68XX_Mini51,SK68XX_Mini11,SK68XX_Mini15,SK68XX_Mini69,SK68XX_Mini31,SK68XX_Mini35,SK68XX_Mini60,SK68XX_Mini33,SK68XX_Mini62,SK68XX_Mini61,SK68XX_Mini73,SK68XX_Mini29,SK68XX_Mini68,SK68XX_Mini52,SK68XX_Mini25,SK68XX_Mini28,SK68XX_Mini54,SK68XX_Mini49,SK68XX_Mini71,SK68XX_Mini72,SK68XX_Mini55,SK68XX_Mini34,SK68XX_Mini13,SK68XX_Mini30,SK68XX_Mini18,SK68XX_Mini9,SK68XX_Mini66";"SK68XXMini_Offset";56;"SK68XXMini";;;
3;"SK68XX_Mini39,SK68XX_Mini41,SK68XX_Mini40,SK68XX_Mini1,SK68XX_Mini38,SK68XX_Mini7,SK68XX_Mini42,SK68XX_Mini3,SK68XX_Mini6,SK68XX_Mini45,SK68XX_Mini44,SK68XX_Mini4,SK68XX_Mini5,SK68XX_Mini43,SK68XX_Mini2,SK68XX_Mini8";"SK68XXMini";16;"SK68XXMini";;;
4;"REF**,REF**";"Mouse_Bite";2;"Mouse_Bite";;;
5;"SW19,SW49";"SW_MX_Hotswap_Rotary_Switch_Rotated";2;"SW_MX_Hotswap_Rotary_Switch_Rotated";;;
6;"SK68XX_Mini27";"SK68XXMini_Short_Offset_for_Rotary_Encoder";1;"SK68XXMini_Short_Offset_for_Rotary_Encoder";;;
7;"SK68XX_Mini64";"SK68XXMini_Short_Offset_for_Rotary_Encoder";1;"SK68XXMini";;;
8;"Ref**";"Junco";1;"Val**";;;
9;"SW29,SW28,SW59,SW58";"SW_MX_HS_1.5u";4;"SW_Push";;;
10;"U2,U4";"SN74AHCT1G125";2;"SN74AHCT1G125";;;
11;"SW24,SW50,SW20,SW32,SW3,SW51,SW37,SW17,SW38,SW31,SW52,SW56,SW27,SW40,SW6,SW46,SW25,SW43,SW14,SW13,SW4,SW16,SW5,SW36,SW21,SW55,SW48,SW18,SW45,SW54,SW39,SW47,SW12,SW26,SW34,SW23,SW10,SW15,SW35,SW57,SW8,SW22,SW44,SW42,SW9,SW41,SW53,SW33,SW11,SW1,SW7,SW2";"SW_MX_HS_1u";52;"SW_Push";;;
12;"FID4,FID1,FID3,FID2";"Fiducial_1mm_Mask2mm";4;"Fiducial";;;
13;"U3,U1";"RPi_Pico_SMD_TH";2;"Pico";;;
14;"J2,J1";"TRRS_PJ320A";2;"AudioJack4";;;
15;"SW30,SW60";"EC11_Rotary_Encoder";2;"RotaryEncoder_Switch";;;

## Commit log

2022-12-21 remove submodule folders
2022-12-21 re-add submodules
2022-12-23 Create raw files dir readme
2022-12-23 Remove random dwl files
2022-12-30 Clean up some traces
2022-12-30 Rename helper file
2023-01-03 Use CERN OHL v2 going forward
2023-01-06 Finish readme + contributing
2023-04-05 Update support status of QMK and VIA
2023-04-08 Update VIA Status
2023-04-29 Keycap rotation Swapped in smd/through-hole diode footprints
2023-04-29 comitt before pcb led rotation unification already updated LED orientation on schematic
2023-04-29 Finished main led flip underglow flip remains
2023-04-29 Added hardware 'handedness on gp18 with default LH
2023-04-30 Updated corner encoders Created flipped encoder/switch combo footprint Created short offset LED for encoder/switch combo Encoder routing Added build notes
2023-05-02 Wiring cleanup
2023-05-03 Routing cleanup
2023-05-03 Removed LED legs and cleaned up routing
2023-05-03 DRC unconnected item repair
2023-05-03 Alined diode orientation updated routing for modified diodes Updated diode labeling
2023-05-03 Removed nested clone
2023-05-05 Added fiducials
2023-05-05 Cleanup for fab switched Diode sides in footprint then on board so it would appear on bottom pos changed pico & rotary encoder component type to fix DRC error generated gerbers generated bom generate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
2023-05-05 Flipped LED footrpints for placement file
2023-05-05 Updated footprints to exclude through-hole components from position files
2023-05-06 Added JLC part number to LED and switch symbols
2023-05-08 DRC rules updated with JLC specs Imported specs from https://github.com/sethhillbrand/kicad_templates Fixed all rule violations increased default vias minor trace cleanup
2023-05-09 Updated minimum annular width Updated copper to edge param updated board accordingly
2023-05-09 Updated copper to hole and hole to hole updated routing accordingly adjusted LED tracks for new via size
2023-05-16 Moved vias off smd pads
2023-05-19 Added level shifter bypass jumper Schematic updated Symbol created and placed
2023-05-21 Culled unused footprints
2023-05-21 Moved under-glow LED's to top side for PNP placement
2023-05-21 Fixed Rotary/switch combo footprint orientation for PNP placement
2023-05-21 Added JLC part numbers to BOM
2023-05-22 Consolidated LED footprints
2023-05-22 Consolidated Switch footprints with 1.5u and 1u
2023-05-22 Updated BOM & PNP
2023-05-22 Updated SK6803 footprint to match tape reel orientation
2023-06-03 Added screen caps from pcb assembly process
2023-06-05 Converted LED outline holes to drill holes tweaked routing for new hole clearance
2023-06-12 Regnerated production files regen gerbers and zipped regen bom/pnp added screencaps for future guide
2023-06-17 build note update
2023-08-10 Checkpoint commit
2023-08-10 Added KiCad PCB Backups folder to gitignore
2023-08-10 First pass at README update General file cleanup moved JLC production guide into seperate folder
2023-09-04 Wrote PCB Assembly build guide
2023-09-04 Moved diode silkscreens to backside
2023-09-04 Updated docs and images for v1.1
2023-09-04 Fixed img size issue in readme
2023-09-05 Updated v1.1 build notes
2023-09-07 Key rotation & other QOL improvements (#2)
    * Keycap rotation
    Swapped in smd/through-hole diode footprints
    * comitt before pcb led rotation unification
    already updated LED orientation on schematic
    * Finished main led flip
    underglow flip remains
2024-06-04 Finally upload custom keymap stuff

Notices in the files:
README.md:
License: CERN Open Hardware Licence v2
